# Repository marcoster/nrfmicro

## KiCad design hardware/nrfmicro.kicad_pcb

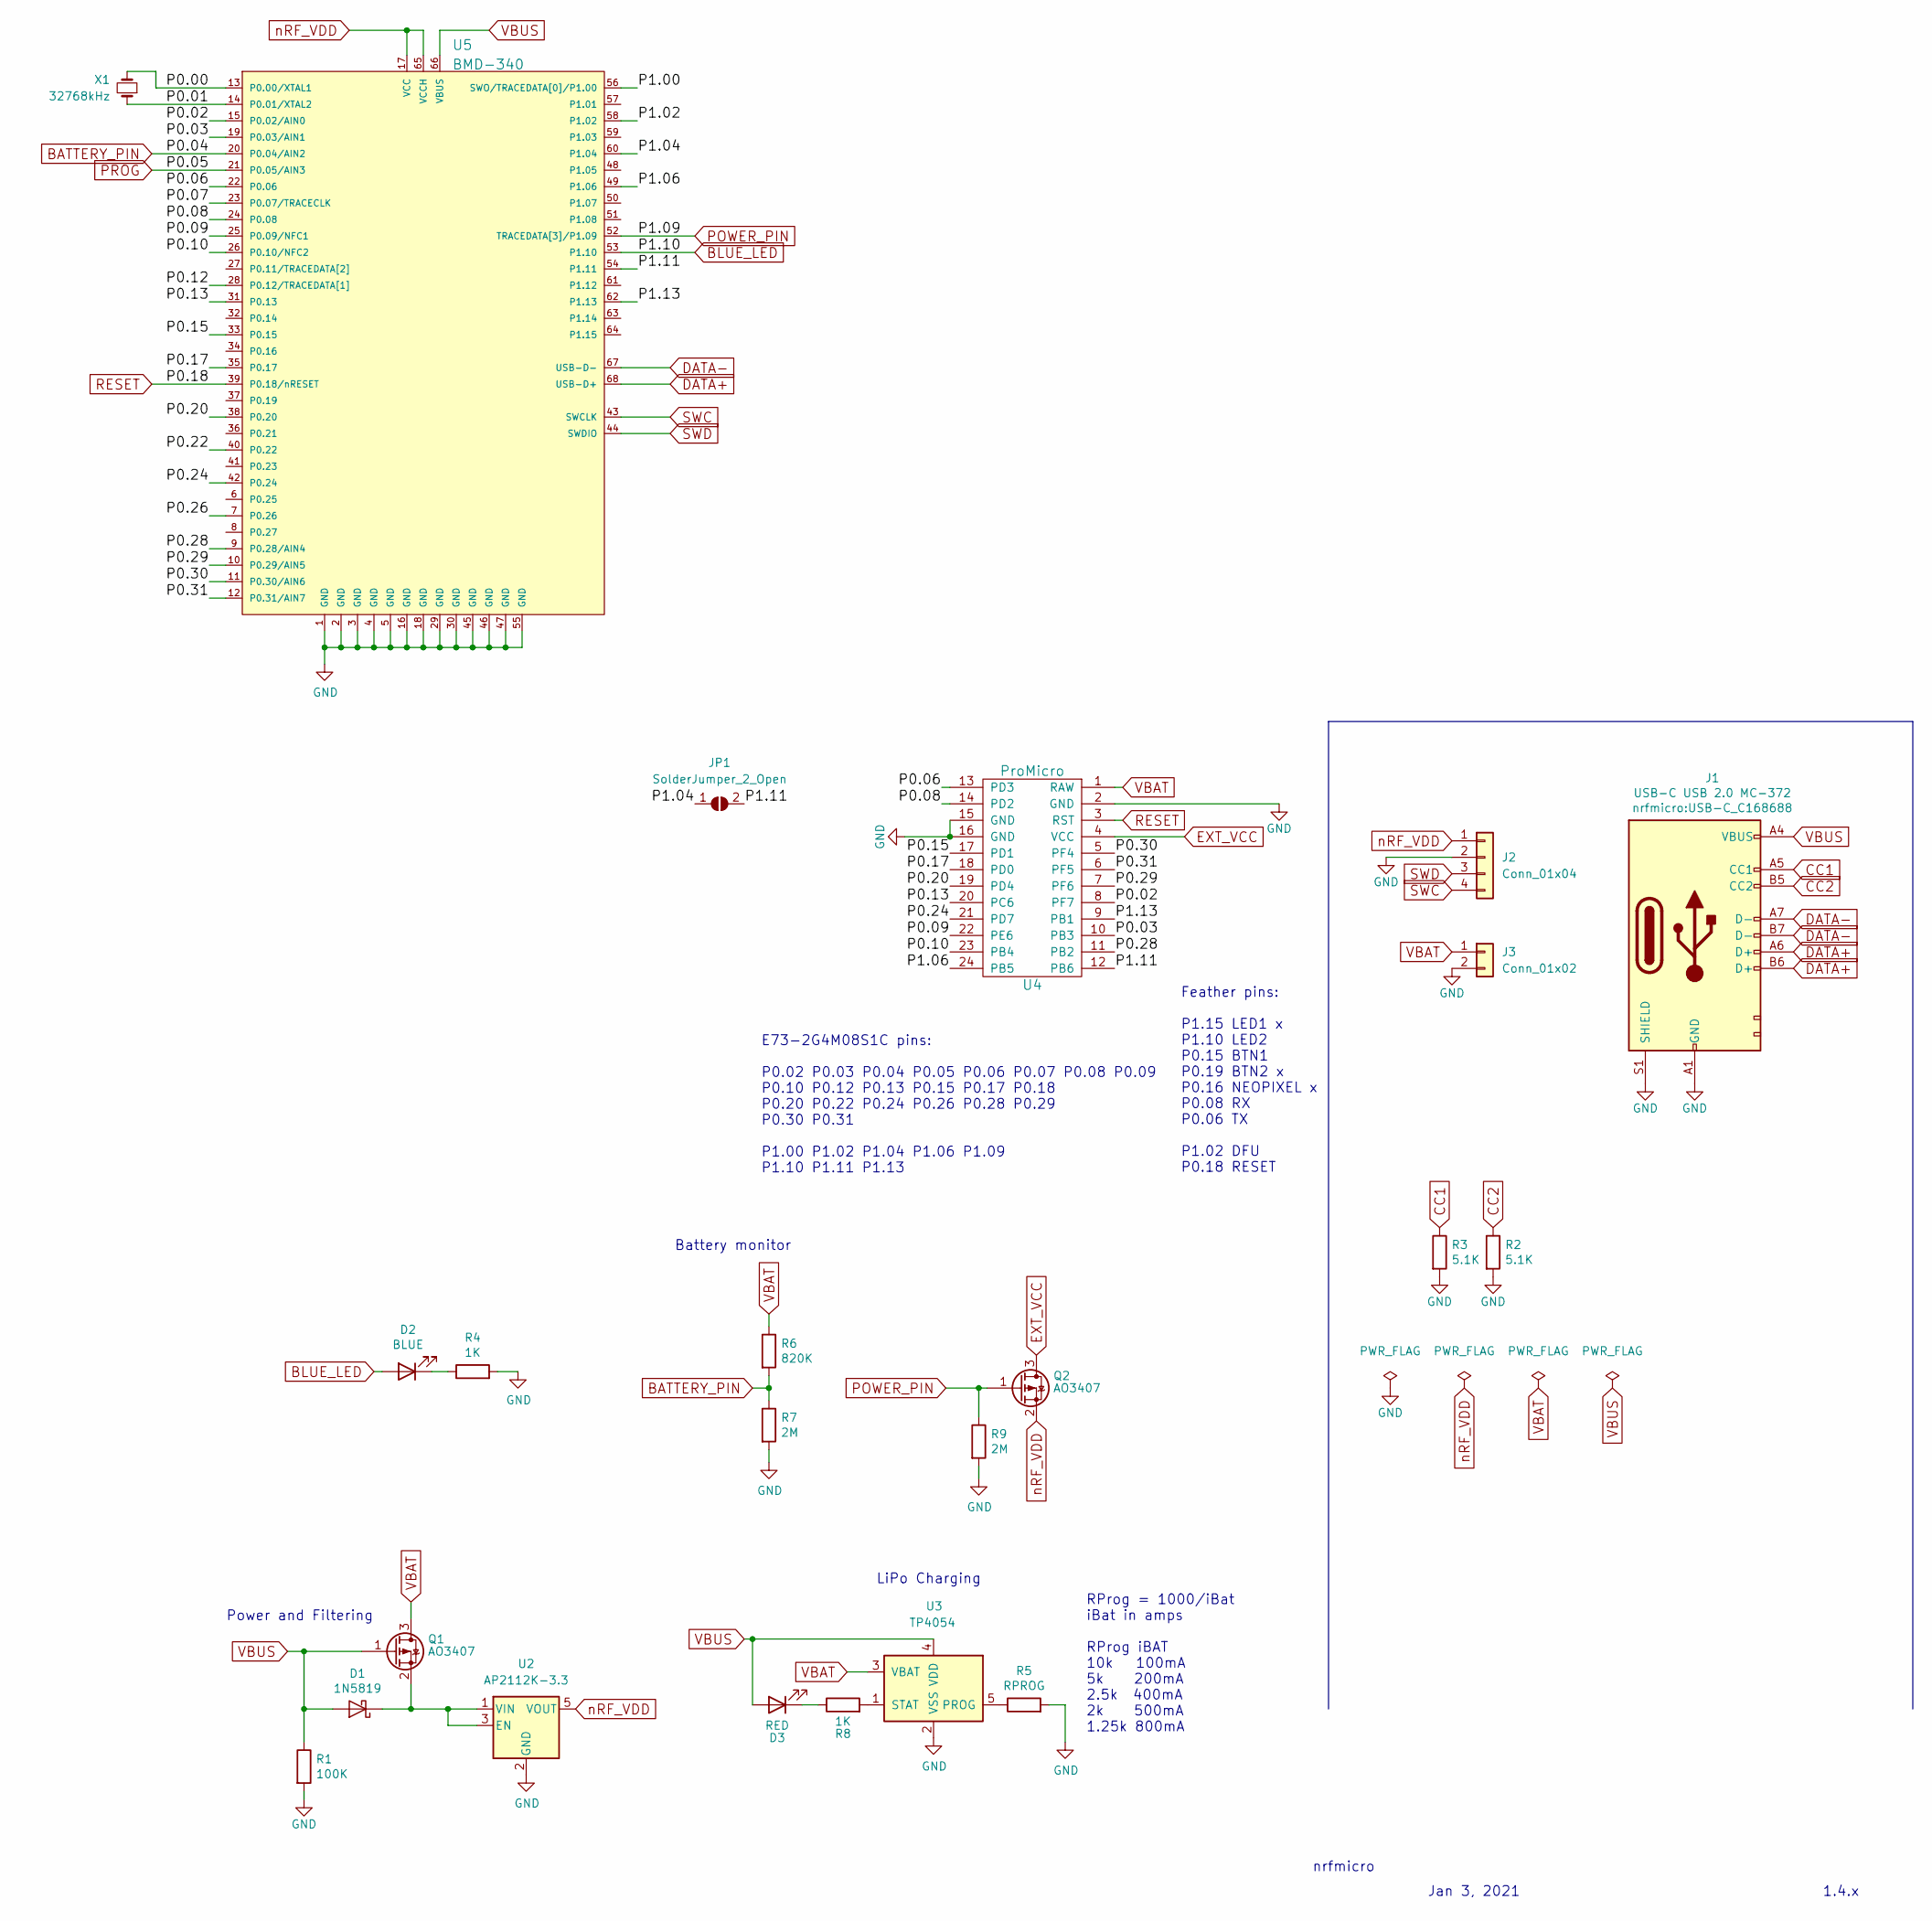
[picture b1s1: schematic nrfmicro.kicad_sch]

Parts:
D1: 1N5819; D_SOD-323F
D2: BLUE; LED_0603_1608Metric
D3: RED; LED_0603_1608Metric
J1: USB-C USB 2.0 MC-372; USB-C_C168688
J2: Conn_01x04; connector_swd
J3: Conn_01x02
JP1: SolderJumper_2_Open; Jumper_SMD
Q1, Q2: AO3407; SOT-23
R1: 100K; R_0603_1608Metric
R2, R3: 5.1K; R_0603_1608Metric
R4, R8: 1K; R_0603_1608Metric
R5: RPROG; R_0603_1608Metric
R6: 820K; R_0603_1608Metric
R7, R9: 2M; R_0603_1608Metric
U2: AP2112K-3.3; SOT-23-5
U3: TP4054; SOT-23-5
U4: ProMicro; pro_micro
U5: BMD-340
X1: 32768kHz

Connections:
/P0.00: U5.13 (P0.00/XTAL1), X1.2
/P0.01: U5.14 (P0.01/XTAL2), X1.1
/P0.02: U4.8 (PF7), U5.15 (P0.02/AIN0)
/P0.03: U4.10 (PB3), U5.19 (P0.03/AIN1)
/P0.06: U4.13 (PD3), U5.22 (P0.06)
/P0.07: U5.23 (P0.07/TRACECLK)
/P0.08: U4.14 (PD2), U5.24 (P0.08)
/P0.09: U4.22 (PE6), U5.25 (P0.09/NFC1)
/P0.10: U4.23 (PB4), U5.26 (P0.10/NFC2)
/P0.12: U5.28 (P0.12/TRACEDATA[1])
/P0.13: U4.20 (PC6), U5.31 (P0.13)
/P0.15: U4.17 (PD1), U5.33 (P0.15)
/P0.17: U4.18 (PD0), U5.35 (P0.17)
/P0.20: U4.19 (PD4), U5.38 (P0.20)
/P0.22: U5.40 (P0.22)
/P0.24: U4.21 (PD7), U5.42 (P0.24)
/P0.26: U5.7 (P0.26)
/P0.28: U4.11 (PB2), U5.9 (P0.28/AIN4)
/P0.29: U4.7 (PF6), U5.10 (P0.29/AIN5)
/P0.30: U4.5 (PF4), U5.11 (P0.30/AIN6)
/P0.31: U4.6 (PF5), U5.12 (P0.31/AIN7)
/P1.00: U5.56 (SWO/TRACEDATA[0]/P1.00)
/P1.02: U5.58 (P1.02)
/P1.04: JP1.1 (A), U5.60 (P1.04)
/P1.06: U4.24 (PB5), U5.49 (P1.06)
/P1.11: JP1.2 (B), U4.12 (PB6), U5.54 (P1.11)
/P1.13: U4.9 (PB1), U5.62 (P1.13)
BATTERY_PIN: R6.2, R7.1, U5.20 (P0.04/AIN2)
BLUE_LED: D2.2 (A), U5.53 (P1.10)
CC1: J1.A5 (CC1), R3.1
CC2: J1.B5 (CC2), R2.1
DATA+: J1.A6 (D+), J1.B6 (D+), U5.68 (USB-D+)
DATA-: J1.A7 (D-), J1.B7 (D-), U5.67 (USB-D-)
EXT_VCC: Q2.3 (D), U4.4 (VCC)
GND: J1.A1 (GND), J1.S1 (SHIELD), J2.2, J3.2, R1.2, R2.2, R3.2, R4.2, R5.2, R7.2, R9.2, U2.2 (GND), U3.2 (VSS), U4.2 (GND), U4.15 (GND), U4.16 (GND), U5.1 (GND), U5.2 (GND), U5.3 (GND), U5.4 (GND), U5.5 (GND), U5.16 (GND), U5.18 (GND), U5.29 (GND), U5.30 (GND), U5.45 (GND), U5.46 (GND), U5.47 (GND), U5.55 (GND)
unnamed: D1.1 (K), Q1.2 (S), U2.1 (VIN), U2.3 (EN)
unnamed: D2.1 (K), R4.1
unnamed: D3.1 (K), R8.1
unnamed: R5.1, U3.5 (PROG)
unnamed: R8.2, U3.1 (STAT)
POWER_PIN: Q2.1 (G), R9.1, U5.52 (TRACEDATA[3]/P1.09)
PROG: U5.21 (P0.05/AIN3)
RESET: U4.3 (RST), U5.39 (P0.18/nRESET)
SWC: J2.4, U5.43 (SWCLK)
SWD: J2.3, U5.44 (SWDIO)
VBAT: J3.1, Q1.3 (D), R6.1, U3.3 (VBAT), U4.1 (RAW)
VBUS: D1.2 (A), D3.2 (A), J1.A4 (VBUS), Q1.1 (G), R1.1, U3.4 (VDD), U5.66 (VBUS)
nRF_VDD: J2.1, Q2.2 (S), U2.5 (VOUT), U5.17 (VCC), U5.65 (VCCH)

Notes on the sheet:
LiPo Charging
Jan 3, 2021
1.4.x
RProg = 1000/iBat iBat in amps RProg iBAT 10k 100mA 5k 200mA 2.5k 400mA 2k 500mA 1.25k 800mA
Power and Filtering
nrfmicro
Battery monitor
E73-2G4M08S1C pins: P0.02 P0.03 P0.04 P0.05 P0.06 P0.07 P0.08 P0.09 P0.10 P0.12 P0.13 P0.15 P0.17 P0.18 P0.20 P0.22 P0.24 P0.26 P0.28 P0.29 P0.30 P0.31 P1.00 P1.02 P1.04 P1.06 P1.09 P1.10 P1.11 P1.13
Feather pins: P1.15 LED1 x P1.10 LED2 P0.15 BTN1 P0.19 BTN2 x P0.16 NEOPIXEL x P0.08 RX P0.06 TX P1.02 DFU P0.18 RESET

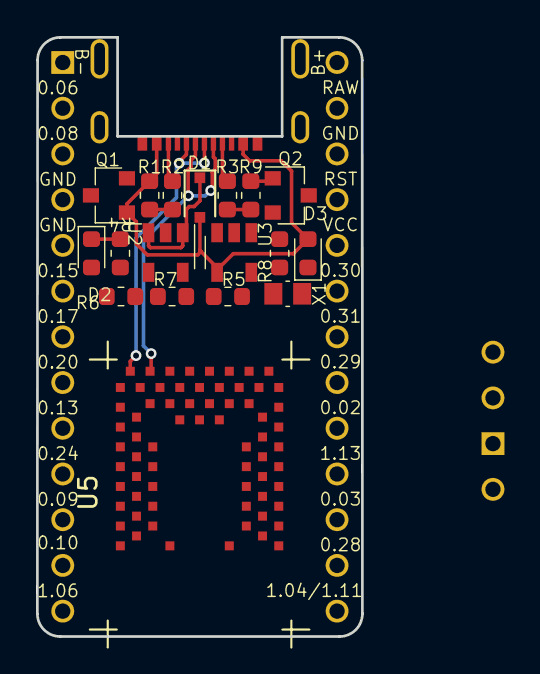
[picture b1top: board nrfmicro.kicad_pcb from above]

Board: 2 copper layers, 18.1 x 33.3 mm, 23 parts (1 on the bottom side), 41 nets.

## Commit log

2022-04-01 bmd-340 variant: start
